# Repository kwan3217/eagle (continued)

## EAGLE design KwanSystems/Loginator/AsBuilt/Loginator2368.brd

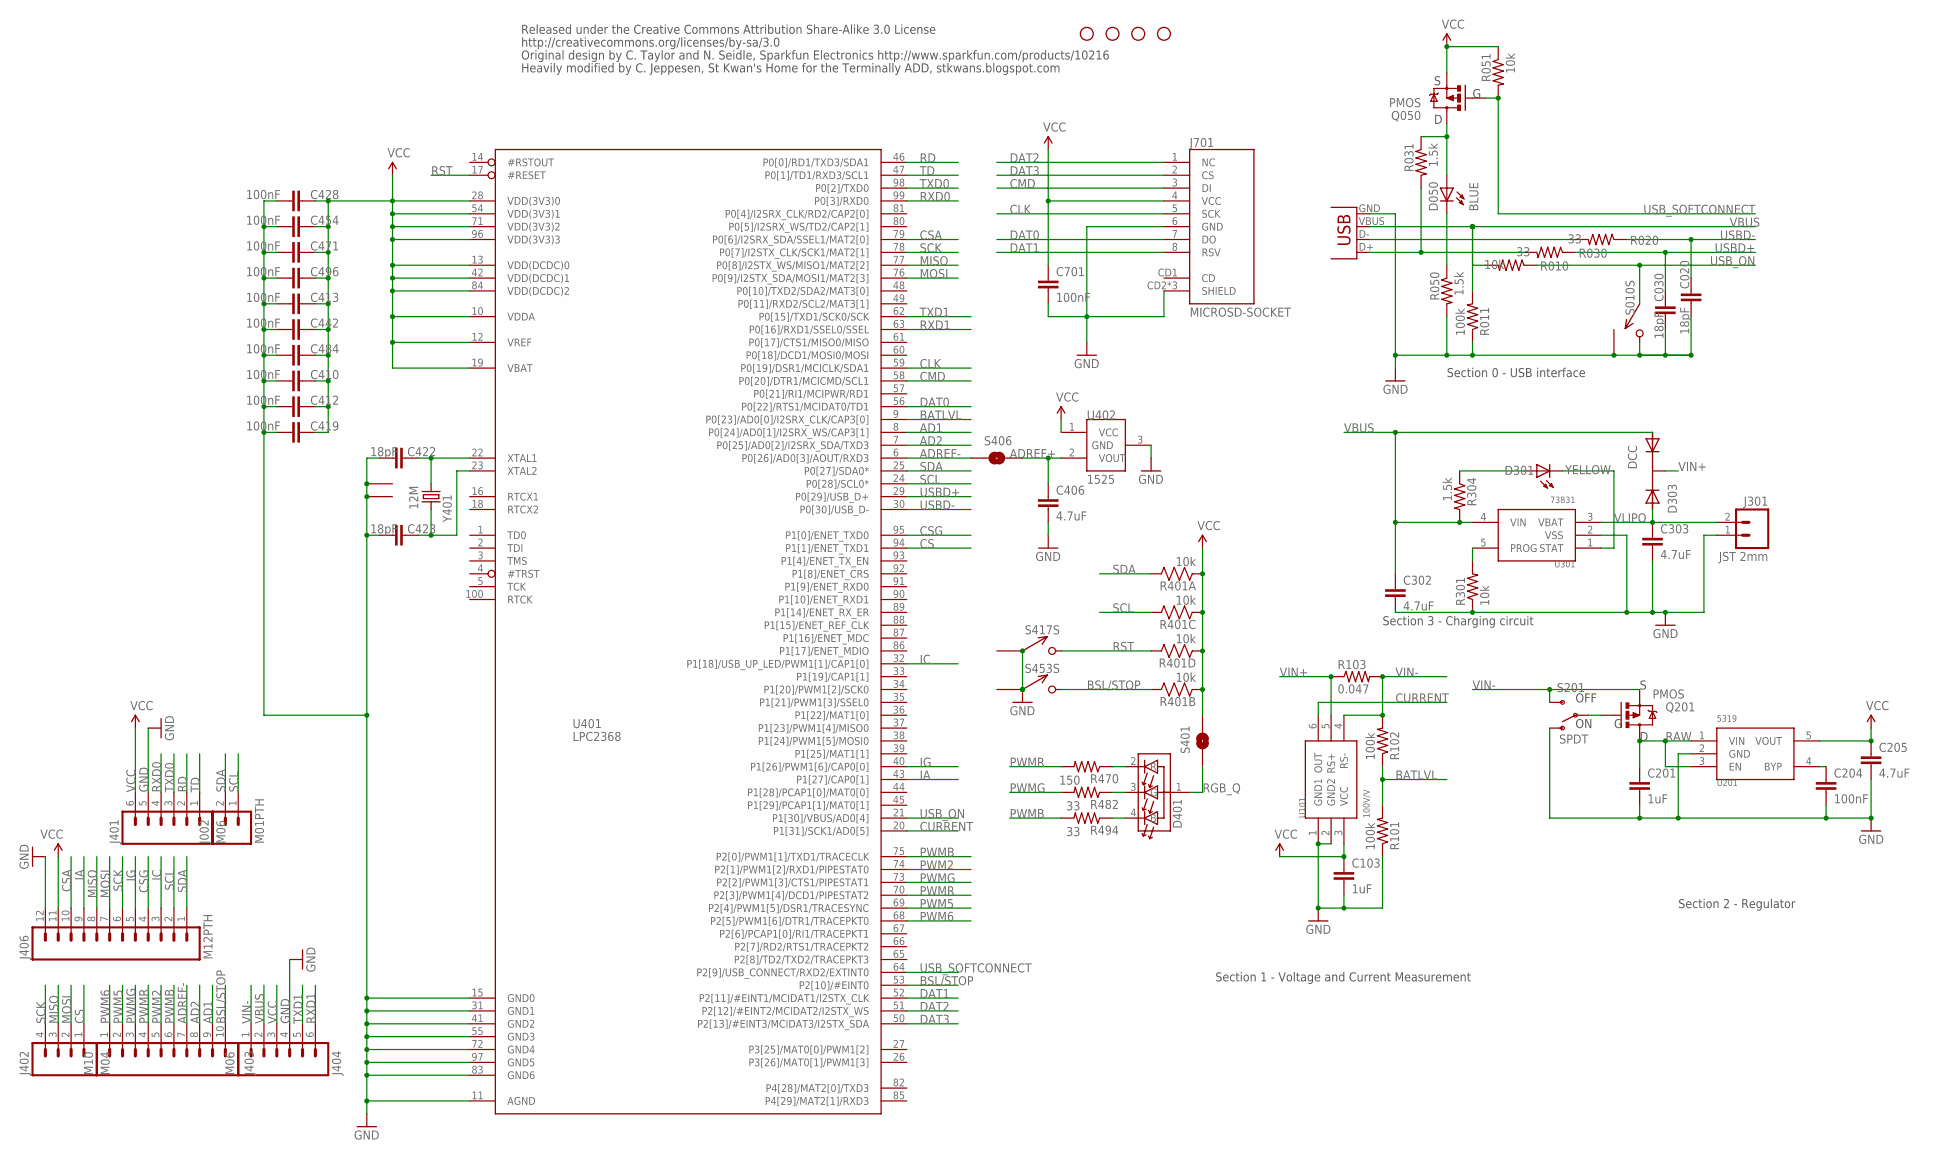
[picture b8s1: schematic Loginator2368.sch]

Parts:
C020, C030, C422, C423: 18pF; 0402-CAP
C103, C201: 1uF; 0402-CAP
C204, C410, C412, C413, C419, C428, C442, C454, C471, C484, C496, C701: 100nF; 0402-CAP
C205, C302, C303, C406: 4.7uF; 0402-CAP
D050: BLUE; LED-0603
D301: YELLOW; LED-0603
D303: DCC; SOT-23-3
D401: RGB; HSMF-C118
J001: USBSMD; USB-MINIB
J002: M01PTH; 1X02
J301: JST 2mm; JST-2-SMD
J401, J404: M06; 1X06
J402: M04; 1X04
J403: M10; 1X10
J406: M12PTH; 1X12
J701: MICROSD-SOCKET; MICROSD-SOCKET-PP
JP1, JP2, JP3, JP4: STAND-OFF
Q050, Q201: PMOS; SOT23-3
R010, R051, R301: 10k; 0402-RES
R011, R101, R102: 100k; 0402-RES
R020, R030, R482, R494: 33; 0402-RES
R031, R050, R304: 1.5k; 0402-RES
R103: 0.047; 0402-RES
R401: 10k; CRA04
R470: 150; 0402-RES
S010, S417, S453: SPST; B3U-1100P
S201: SPDT; AYZ0202
S401, S406: SOLDERJUMPERNO; SJ_2S-NO
U101: 100V/V; SOT-23-6
U201: 5319; SOT-23-5
U301: 73831; SOT-23-5
U401: LPC2368; LQFP100
U402: 1525; SOT-23-3
Y401: 12M; CRYSTAL_SMD

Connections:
AD1: J403.9, U401.8 (P0[24]/AD0[1]/I2SRX_WS/CAP3[1])
AD2: J403.8, U401.7 (P0[25]/AD0[2]/I2SRX_SDA/TXD3)
ADREF+: C406.1, S406.1, U402.2 (VOUT)
ADREF-: J403.7, S406.2, U401.6 (P0[26]/AD0[3]/AOUT/RXD3)
BATLVL: R101.2, R102.1, U401.9 (P0[23]/AD0[0]/I2SRX_CLK/CAP3[0])
BSL/STOP: J403.10, R401.7 (2), S453.P$2 (2), U401.53 (P2[10]/#EINT0)
CLK: J701.5 (SCK), U401.59 (P0[19]/DSR1/MCICLK/SDA1)
CMD: J701.3 (DI), U401.58 (P0[20]/DTR1/MCICMD/SCL1)
CONN_D+: J001.D+, R030.2, R031.2
CONN_D-: J001.D-, R020.2
CS: J402.1, U401.94 (P1[1]/ENET_TXD1)
CSA: J406.10, U401.79 (P0[6]/I2SRX_SDA/SSEL1/MAT2[0])
CSG: J406.4, U401.95 (P1[0]/ENET_TXD0)
CURRENT: U101.6 (OUT), U401.20 (P1[31]/SCK1/AD0[5])
DAT0: J701.7 (DO), U401.56 (P0[22]/RTS1/MCIDAT0/TD1)
DAT1: J701.8 (RSV), U401.52 (P2[11]/#EINT1/MCIDAT1/I2STX_CLK)
DAT2: J701.1 (NC), U401.51 (P2[12]/#EINT2/MCIDAT2/I2STX_WS)
DAT3: J701.2 (CS), U401.50 (P2[13]/#EINT3/MCIDAT3/I2STX_SDA)
DB: D401.4 (B), R494.1
DG: D401.3 (G), R482.1
DR: D401.2 (R), R470.1
GND: C020.2, C030.2, C103.2, C201.2, C204.2, C205.2, C302.2, C303.2, C406.2, C410.2, C412.2, C413.2, C419.2, C422.1, C423.1, C428.2, C442.2, C454.2, C471.2, C484.2, C496.2, C701.2, J001.GND, J301.1, J401.5, J404.4, J406.12, J701.6 (GND), J701.CD2 (SHIELD), J701.GND1 (SHIELD), J701.GND3 (SHIELD), R011.1, R050.2, R101.1, R301.1, S010.P$2 (2), S010.P$3 (1), S201.1 (O), S417.P$1 (1), S417.P$3 (1), S453.P$1 (1), S453.P$3 (1), U101.1 (GND1), U101.2 (GND2), U201.2 (GND), U301.2 (VSS), U401.11 (AGND), U401.15 (GND0), U401.31 (GND1), U401.41 (GND2), U401.55 (GND3), U401.72 (GND4), U401.83 (GND6), U401.97 (GND5), U402.3 (GND), Y401.2 (1), Y401.4 (1)
IA: J406.9, U401.43 (P1[27]/CAP0[1])
IC: J406.3, U401.32 (P1[18]/USB_UP_LED/PWM1[1]/CAP1[0])
IG: J406.5, U401.40 (P1[26]/PWM1[6]/CAP0[0])
MISO: J402.3, J406.8, U401.77 (P0[8]/I2STX_WS/MISO1/MAT2[2])
MOSI: J402.2, J406.7, U401.76 (P0[9]/I2STX_SDA/MOSI1/MAT2[3])
unnamed: D301.A, R304.1
unnamed: R301.2, U301.5 (PROG)
unnamed: D301.C, U301.1 (STAT)
unnamed: D050.A, Q050.3 (D), R031.1
unnamed: D050.C, R050.1
unnamed: Q201.1 (G), S201.2
unnamed: C204.1, U201.4 (BYP)
PWM2: J403.5, U401.74 (P2[1]/PWM1[2]/RXD1/PIPESTAT0)
PWM5: J403.2, U401.69 (P2[4]/PWM1[5]/DSR1/TRACESYNC)
PWM6: J403.1, U401.68 (P2[5]/PWM1[6]/DTR1/TRACEPKT0)
PWMB: J403.6, R494.2, U401.75 (P2[0]/PWM1[1]/TXD1/TRACECLK)
PWMG: J403.3, R482.2, U401.73 (P2[2]/PWM1[3]/CTS1/PIPESTAT1)
PWMR: J403.4, R470.2, U401.70 (P2[3]/PWM1[4]/DCD1/PIPESTAT2)
RAW: C201.1, Q201.3 (D), U201.1 (VIN), U201.3 (EN)
RD: J401.2, U401.46 (P0[0]/RD1/TXD3/SDA1)
RGB_Q: D401.1 (A), S401.1
RST: R401.5 (2), S417.P$2 (2), U401.17 (#RESET)
RXD0: J401.4, U401.99 (P0[3]/RXD0)
RXD1: J404.6, U401.63 (P0[16]/RXD1/SSEL0/SSEL)
SCK: J402.4, J406.6, U401.78 (P0[7]/I2STX_CLK/SCK1/MAT2[1])
SCL: J002.1, J406.2, R401.6 (2), U401.24 (P0[28]/SCL0*)
SDA: J002.2, J406.1, R401.8 (2), U401.25 (P0[27]/SDA0*)
TD: J401.1, U401.47 (P0[1]/TD1/RXD3/SCL1)
TXD0: J401.3, U401.98 (P0[2]/TXD0)
TXD1: J404.5, U401.62 (P0[15]/TXD1/SCK0/SCK)
USBD+: C030.1, R030.1, U401.29 (P0[29]/USB_D+)
USBD-: C020.1, R020.1, U401.30 (P0[30]/USB_D-)
USB_ON: R010.1, S010.P$1 (1), U401.21 (P1[30]/VBUS/AD0[4])
USB_SOFTCONNECT: Q050.1 (G), R051.2, U401.64 (P2[9]/USB_CONNECT/RXD2/EXTINT0)
VBUS: C302.1, D303.1 (A1), J001.VBUS, J404.2, R010.2, R011.2, R304.2, U301.4 (VIN)
VCC: C103.1, C205.1, C410.1, C412.1, C413.1, C419.1, C428.1, C442.1, C454.1, C471.1, C484.1, C496.1, C701.1, J401.6, J404.3, J406.11, J701.4 (VCC), Q050.2 (S), R051.1, R401.1, R401.2 (1), R401.3 (1), R401.4 (1), S401.2, U101.3 (VCC), U201.5 (VOUT), U401.10 (VDDA), U401.12 (VREF), U401.13 (VDD(DCDC)0), U401.19 (VBAT), U401.28 (VDD(3V3)0), U401.42 (VDD(DCDC)1), U401.54 (VDD(3V3)1), U401.71 (VDD(3V3)2), U401.84 (VDD(DCDC)2), U401.96 (VDD(3V3)3), U402.1 (VCC)
VIN+: D303.3 (K), R103.1, U101.5 (RS+)
VIN-: J404.1, Q201.2 (S), R102.2, R103.2, S201.3 (S), U101.4 (RS-)
VLIPO: C303.1, D303.2 (A2), J301.2, U301.3 (VBAT)
XTAL1: C422.2, U401.22 (XTAL1), Y401.3 (2)
XTAL2: C423.2, U401.23 (XTAL2), Y401.1

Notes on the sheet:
Section 2 - Regulator
Section 3 - Charging circuit
Section 0 - USB interface
Released under the Creative Commons Attribution Share-Alike 3.0 License
http://creativecommons.org/licenses/by-sa/3.0
Original design by C. Taylor and N. Seidle, Sparkfun Electronics http://www.sparkfun.com/products/10216
Heavily modified by C. Jeppesen, St Kwan's Home for the Terminally ADD, stkwans.blogspot.com
Section 1 - Voltage and Current Measurement
OFF

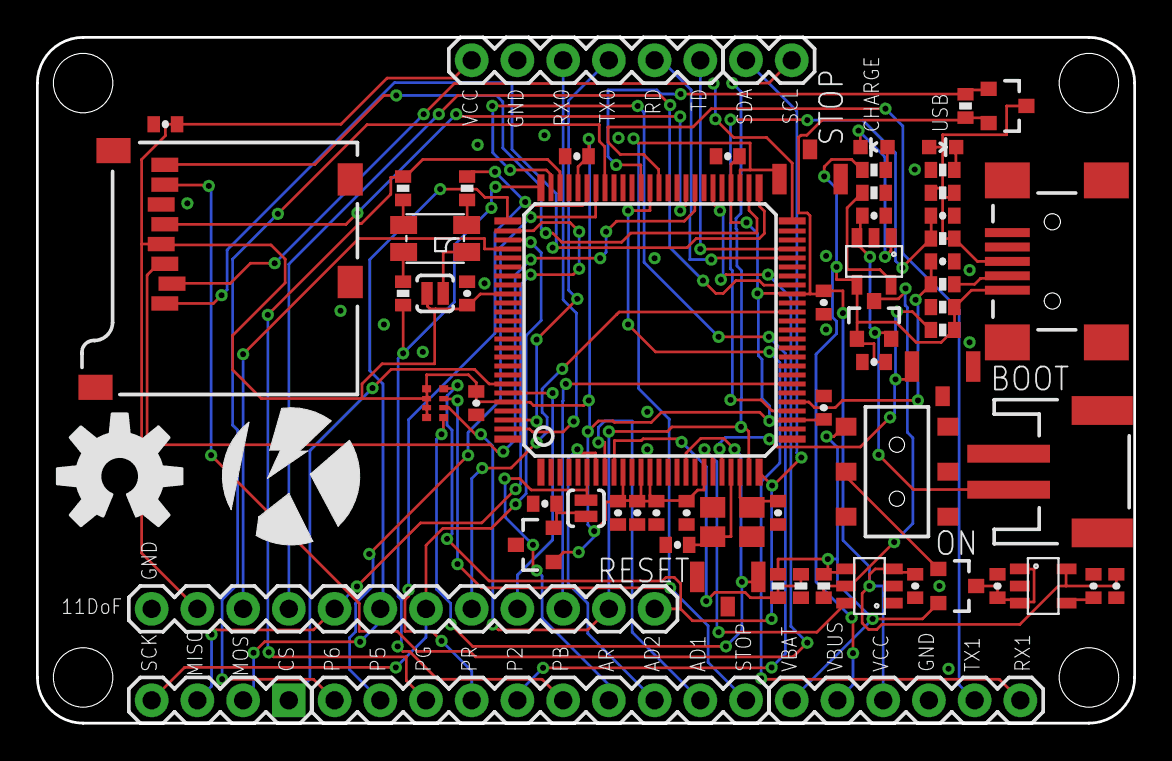
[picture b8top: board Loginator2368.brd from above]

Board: 2 copper layers, 61.0 x 38.1 mm, 71 parts (0 on the bottom side), 63 nets.

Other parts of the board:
U$1: KWAN_CIRCLE
U$2: OSHW-LOGO-L

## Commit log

2012-08-08 Initial commit (into git)
2012-08-09 Initial commit (to git)
2012-09-14 IMUinator was just a copy of Logomatic. Added a .gitignore file. Updated Precision to have all the LEDs in the right color so that add-digikey.ulp works properly.
2012-09-14 Removed experimental files 11DoF half and 6Dof. Neither is needed with working 11DoF
2012-09-14 Cleanroom Nano before shifting positions of ATMega and FT232
2012-09-14 FT232 close to USB port, ATMega still diagonal
2012-09-15 No regulator, with top labels
2012-09-15 Renamed Cleanroom Nano to Naninator
2012-09-17 Rescued from Osaka working copy
2012-09-17 Naninator with regulator on top side, some .gitignore fixes
2012-09-17 Digikey part numbers for Naninator. Added the MicroSMP diode to eagle3d.
2012-09-20 Merged Mio's KwanSystems.lbr, updated all eagle files to use it.
2012-09-28 All 11DoF sensors working
2012-09-28 Made 11DoF for BMA180, MPU6000, replaced ADXL345 with BMA180 in Rocketometer2148, made Rocketometer2148 with MPU6000
2012-10-29 Split off hardware stack initialization and checking
2012-10-30 Finished routing of board
2012-10-30 Further cleanup of board
2012-10-31 Flip card slot to opposite side of board, shorten board
2012-11-02 Finished routing shorter board
2012-11-13 RocketometerMPU sent to Laen
2012-11-18 Packaging for push
2012-11-19 Rocketometer6050 fully routed, almost fully manually
2012-11-19 In preparation for adding more resistor arrays to power supply
2012-11-20 RocketometerMPU6050 as ordered
2012-11-20 14DoF ready to process
2012-11-21 Started on Nano Leonardo
2012-11-28 Added KwanAstro after the little crash of 2012
2012-11-28 14DoF etc
2012-12-21 packing for trip to Oklahoma
2013-01-26 Include Win32 CSPICE to handle ephemeris for BPlane MFD
2013-01-28 Lots of changes to BPlane. Added bypass caps to RxPx
2013-01-29 Added the DigitalMisery AltStick and Sparkfun Propeller breakout
2013-02-01 Got the ISO date format in the Docs library
2013-02-01 Fixed author information
2013-02-02 Rotated Px chip 90deg and rerouted 90% manually
2013-02-02 Redid some of the labels
2013-02-04 Satisfactory RkPx. Added BTC 2.32 with intent to fix and publish as 2.4
2013-02-06 Modified Loginator to use more resistor arrays
2013-02-07 Auto-routed R2148-9150
2013-02-13 Added Maven spice kernels
2013-02-24 As (attempted to be) flown 23 Feb 2013
2013-02-24 Packed for trip to Maryland
2013-03-26 USB Docs and Rocketometer patch
2013-03-26 Added TMA2 project, updated Sparkfun libraries
2013-04-13 Added in-ram logger to Pinewood
2013-04-14 moved PEG from work to Kwan workspace
2013-04-29 DirectTask and Rocketometer which uses it
2013-05-28 Preparing for check against workspace~ and workspace2
2013-05-28 New version of rocketometer board for production
2013-05-29 Started Precision ATMega32U4
2013-05-29 Started RocketometerATMega.sch, finished PrecisionATMega32U4
2013-05-30 Further progress on the RocketometerATMega
2013-06-25 Pushing back eagle changes
2013-09-20 Restored digikey.dat (don't use git rm to resolve a conflict)
2013-09-20 Flight 36.290 version of Rocketometer restored, Black Brant filter created
2013-09-25 Added Precision Arduino 7400
2013-09-26 Finished connecting hands, ripped up the rest of thw wires
2013-09-26 Rewired the left side 3-5 gates
2013-09-27 Added Nano Leonardo no 3V3
2013-09-27 Converted certain Sparkfun schematics to XML
2013-09-27 Got latest version of Sparkfun libraries from github
2013-10-01 Lots of work on Android things
2013-10-02 Reorganized eagle/KwanSystems
2013-10-05 Java implementation of Rocketometer filter
2013-10-26 Working on ellipsoid fit for soft iron
2013-11-09 First cut at GPS parser - written with pointers to member functions
2013-11-14 Added two-transistor NMOS array, and started GP2106 adapter for Rocketometer
2013-11-25 Florida4 version of Pocketometer
2013-11-27 Checked in Florida4 data
2013-12-19 More work on pure vector XR2 skin
2014-01-09 Shuffled several documents
2014-02-05 Pushing it all as a backup
2014-03-14 Labeled Loginator 11DoF ports
2014-03-14 Pinewood got a mind transplant from Rocketometer
2014-03-19 Branched Rocketometer off into Yukari
2014-03-21 More work on Yukari, replaced transistor with my own library, which includes SC70 package
2014-03-21 Added Pinewood bench data and K2
2014-03-28 Finally found a complete solution
2014-04-16 Added new feature to NavCalc
2014-04-27 One Shining Moment - PWMExample1 can steer Yukari
2014-05-18 Added encryption to NavCalc
2014-06-18 Starting final push on YukariII
2014-06-24 Started Yukari 3
2014-06-24 More work to Yukari3
2014-06-25 Added Yukari 3 9150, with integrated 11DoF
2014-06-26 More changes to Yukari 3
2014-06-29 Added Tomo, display/button board for Yukari robot controller
2014-06-29 Removing binary version of NCP1402
2014-06-30 Cleanup
2014-07-11 Reorganized docs for ARM. Added engine rooms with AD magnetic couplers instead of optocouplers.
2014-07-11 Fixed switch direction
2014-07-14 Split up
2014-11-04 Added LegoClassicSpace.svg after checking local copy. We'll see how the pull works
2014-11-05 Refactored repository, preparatory to splitting into code and data repositories
2015-06-27 Remove and rename in preparation for BFG
2015-10-08 Moved sinTable so that only one copy of it is ever used
2015-12-03 Added Yukari4, changed it over to use templates
2015-12-03 Added eagle changes made on Mio
2015-12-03 Added updated Sparkfun stuff
2016-01-04 Refactored SimSd to have transferMISO and transferMOSI separated
2016-02-09 Pushing back
2016-02-10 More cortex-M4 startup stuff
2016-08-18 Adding Yukari4 Naninator board, and adding a couple of isolators to the library
2016-08-19 More progress
2017-04-10 Added Tomo5, a hat for a Pi that holds a GPS, MPU, Arduino, etc. Replaces the whole red board in Yukari
2017-04-17 Added Adafruit stuff
2017-08-09 Changing over the Adafruit stuff to submodules
2017-08-09 Adding Adafruit stuff as submodules
